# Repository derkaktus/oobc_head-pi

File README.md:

# OutofBand Console Server Head for Raspberry Pi

Upgrade your Raspberry Pi to an eight port serial console server for OoB management.

<br clear="left"/>
<br clear="right"/>

## Function
The head utilizes the build in UART capability of the raspberry pi (only UART0) and adds the 8 port switching capability. 
The port can be selected via pin 16, 18 and 22 a.k.a. **GPIO 22, 23** and **25** by adjusting their HIGH LOW state.

| PORT |GPIO>  | 22 | 23 | 25 |
|--|--| -- | -- | -- |
| 1 |  | 0 | 0 | 0 |
| 2 |  | 1 | 0 | 0 |
| 3 |  | 0 | 1 | 0 |
| 4 |  | 1 | 1 | 0 |
| 5 |  | 0 | 0 | 1 |
| 6 |  | 1 | 0 | 1 |
| 7 |  | 0 | 1 | 1 |
| 8 |  | 1 | 1 | 1 |

## Component
- 1x Pin Header 2x20 for Raspberry Pi
- 2x CD4051BE IC (Analog Multiplexer Single 8)

Optional: 
- 2x IC Socket 16 / 2x8 pin

Watch for the 2.54 mm pitch versions !!

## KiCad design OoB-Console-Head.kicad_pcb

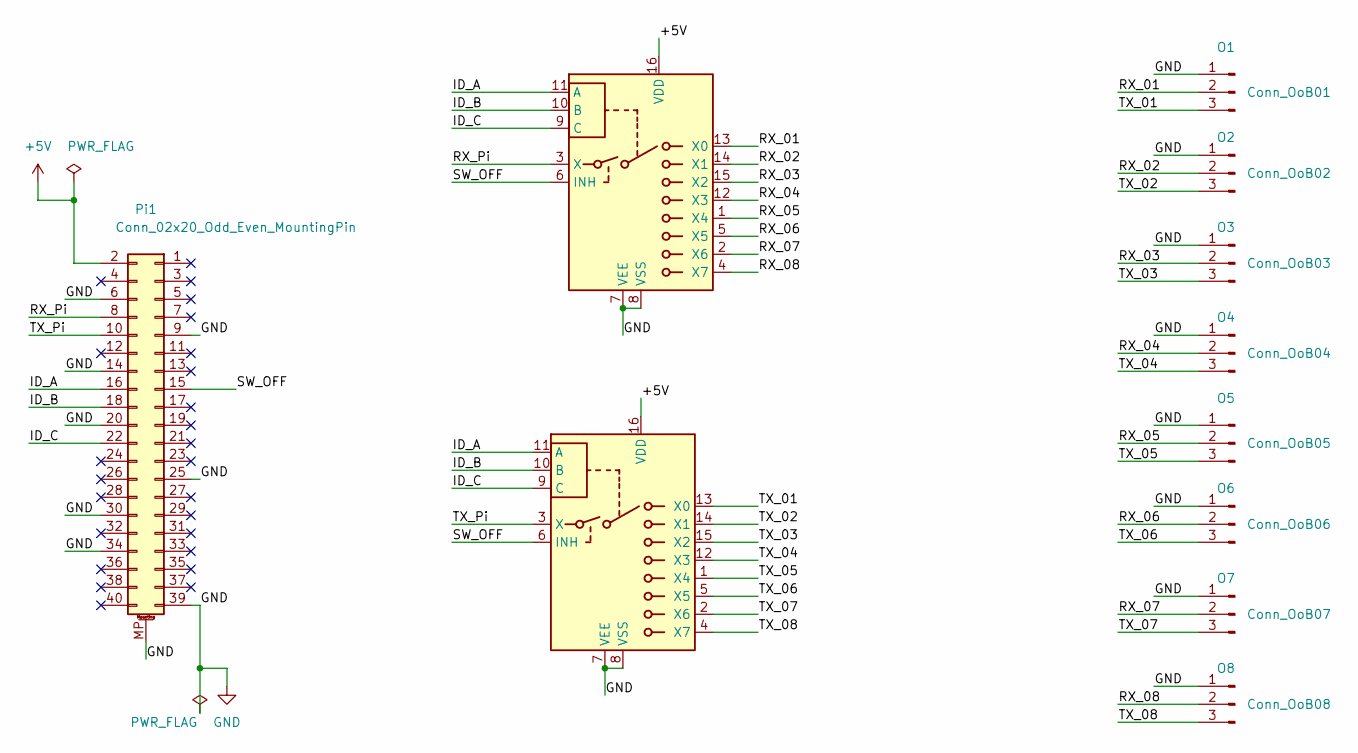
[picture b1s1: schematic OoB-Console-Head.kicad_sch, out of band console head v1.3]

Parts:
O1: Conn_OoB01; PinHeader_1x03_P2.54mm_Horizontal
O2: Conn_OoB02; PinHeader_1x03_P2.54mm_Horizontal
O3: Conn_OoB03; PinHeader_1x03_P2.54mm_Horizontal
O4: Conn_OoB04; PinHeader_1x03_P2.54mm_Horizontal
O5: Conn_OoB05; PinHeader_1x03_P2.54mm_Horizontal
O6: Conn_OoB06; PinHeader_1x03_P2.54mm_Horizontal
O7: Conn_OoB07; PinHeader_1x03_P2.54mm_Horizontal
O8: Conn_OoB08; PinHeader_1x03_P2.54mm_Horizontal
Pi1: Conn_02x20_Odd_Even_MountingPin; PinSocket_2x20_P2.54mm_Vertical
RX1: CD4051B; CD4051
TX1: CD4051B; CD4051

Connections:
+5V: Pi1.2, RX1.16 (VDD), TX1.16 (VDD)
/ID_A: Pi1.16, RX1.11 (A), TX1.11 (A)
/ID_B: Pi1.18, RX1.10 (B), TX1.10 (B)
/ID_C: Pi1.22, RX1.9 (C), TX1.9 (C)
/RX_01: O1.2, TX1.13 (X0)
/RX_02: O2.2, TX1.14 (X1)
/RX_03: O3.2, TX1.15 (X2)
/RX_04: O4.2, TX1.12 (X3)
/RX_05: O5.2, TX1.1 (X4)
/RX_06: O6.2, TX1.5 (X5)
/RX_07: O7.2, TX1.2 (X6)
/RX_08: O8.2, TX1.4 (X7)
/RX_Pi: Pi1.8, TX1.3 (X)
/SW_OFF: Pi1.15, RX1.6 (INH), TX1.6 (INH)
/TX_01: O1.3, RX1.13 (X0)
/TX_02: O2.3, RX1.14 (X1)
/TX_03: O3.3, RX1.15 (X2)
/TX_04: O4.3, RX1.12 (X3)
/TX_05: O5.3, RX1.1 (X4)
/TX_06: O6.3, RX1.5 (X5)
/TX_07: O7.3, RX1.2 (X6)
/TX_08: O8.3, RX1.4 (X7)
/TX_Pi: Pi1.10, RX1.3 (X)
GND: O1.1, O2.1, O3.1, O4.1, O5.1, O6.1, O7.1, O8.1, Pi1.6, Pi1.9, Pi1.14, Pi1.20, Pi1.25, Pi1.30, Pi1.34, Pi1.39, Pi1.MP (MountPin), RX1.7 (VEE), RX1.8 (VSS), TX1.7 (VEE), TX1.8 (VSS)

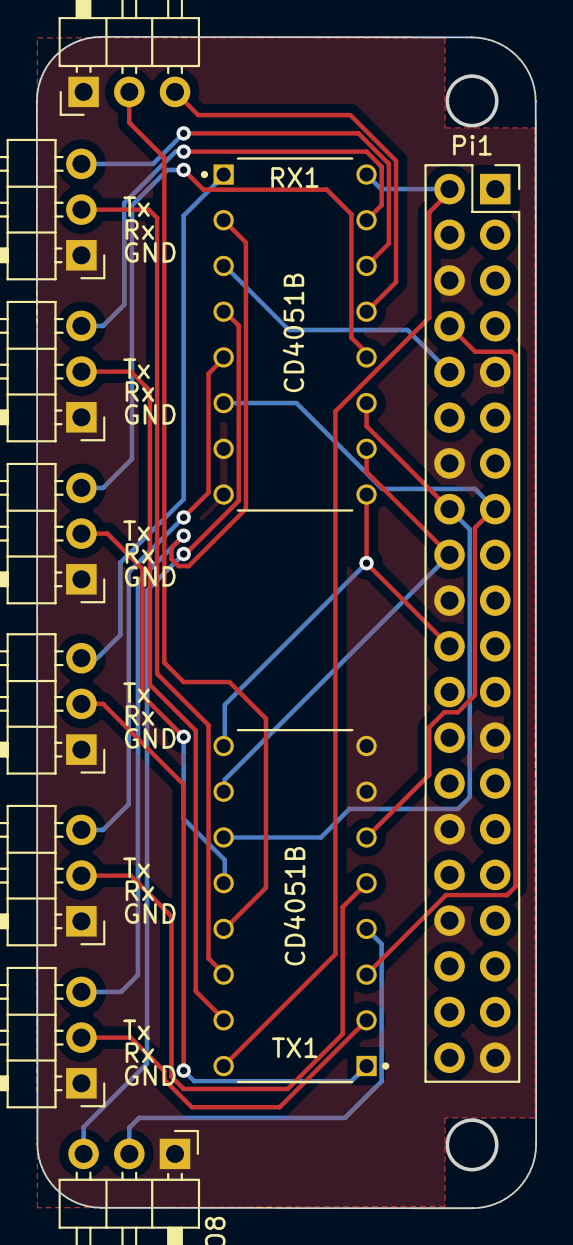
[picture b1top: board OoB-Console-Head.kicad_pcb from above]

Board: 2 copper layers, 27.6 x 65.0 mm, 11 parts (0 on the bottom side), 24 nets.

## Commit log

2024-02-12 Update README.md
    Adjusting title and repository name
2024-05-09 Update README.md
    Updated for Version 1.2
